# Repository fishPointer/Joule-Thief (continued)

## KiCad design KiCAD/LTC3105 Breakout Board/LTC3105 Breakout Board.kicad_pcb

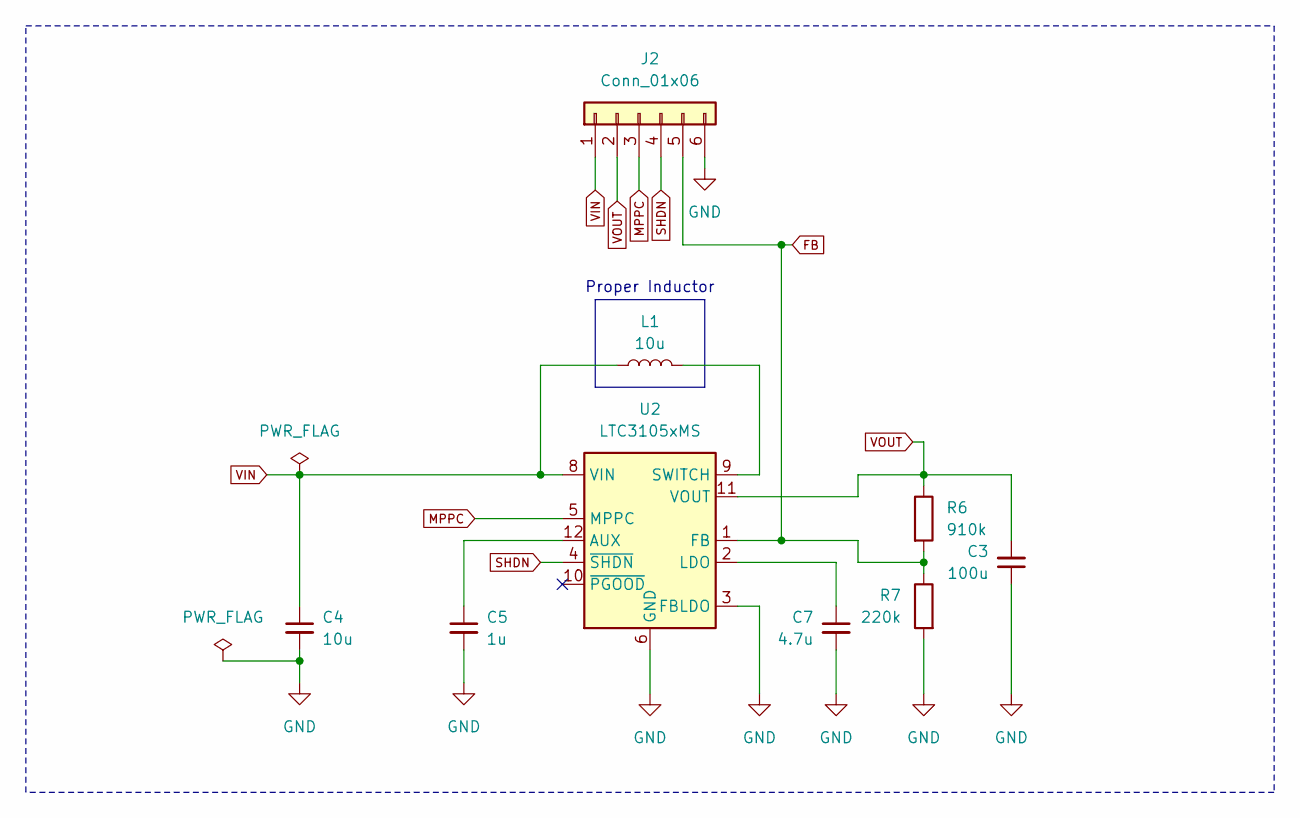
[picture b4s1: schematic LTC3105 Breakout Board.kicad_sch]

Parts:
C3: 100u; C_0805_2012Metric_Pad1.18x1.45mm_HandSolder
C4: 10u; C_0805_2012Metric_Pad1.18x1.45mm_HandSolder
C5: 1u; C_0805_2012Metric_Pad1.18x1.45mm_HandSolder
C7: 4.7u; C_0805_2012Metric_Pad1.18x1.45mm_HandSolder
J2: Conn_01x06; PinHeader_1x06_P1.27mm_Vertical
L1: 10u; Power_Inductor_101040
R6: 910k; PinHeader_1x02_P1.27mm_Vertical
R7: 220k; R_0805_2012Metric_Pad1.20x1.40mm_HandSolder
U2: LTC3105xMS; MSOP-12_3x4.039mm_P0.65mm

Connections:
FB: J2.5, R6.2, R7.1, U2.1 (FB)
GND: C3.1, C4.2, C5.2, C7.2, J2.6, R7.2, U2.3 (FBLDO), U2.6 (GND), U2.7 (GND)
MPPC: J2.3, U2.5 (MPPC)
unnamed: C5.1, U2.12 (AUX)
unnamed: C7.1, U2.2 (LDO)
unnamed: L1.2, U2.9 (SWITCH)
SHDN: J2.4, U2.4 (~SHDN)
VIN: C4.1, J2.1, L1.1, U2.8 (VIN)
VOUT: C3.2, J2.2, R6.1, U2.11 (VOUT)

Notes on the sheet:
Proper Inductor

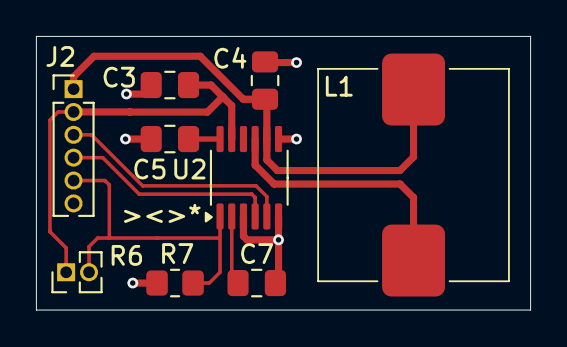
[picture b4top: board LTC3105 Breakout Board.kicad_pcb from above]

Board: 2 copper layers, 27.4 x 15.2 mm, 9 parts (0 on the bottom side), 9 nets.

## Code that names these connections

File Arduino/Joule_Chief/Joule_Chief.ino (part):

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bool schmittState = false;                  // Current state of Schmitt trigger output

// Charger Buffer Schmitt Trigger Parameters
const float SCHMITT_UPPER_THRESHOLD_2 = 5.25; // Upper threshold voltage for boost
const float SCHMITT_LOWER_THRESHOLD_2 = 4.25; // Lower threshold voltage for boost
bool schmittState2 = false;                    // Current state of second Schmitt trigger output

// ----------- DECLARATIONS -----------
// Analog and Digital I/O Pin Definitions
const int BOOST_PIN = 5;    // Chief Booster Enable HIGH
const int CHARGE_PIN = 6;   // Chief Charger Enable HIGH
const int SHDN_0_PIN = 13;  // Pull LOW to SHDN Module 0
const int SHDN_1_PIN = 12;  // Pull LOW to SHDN Module 1
const int SHDN_2_PIN = 11;  // Pull LOW to SHDN Module 2
const int SHDN_3_PIN = 10;  // Pull LOW to SHDN Module 3

// ----------- CHANNEL DATA STRUCTURE -----------
struct ChannelData {
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  Wire.setClock(400000);  // Set I2C clock to 400kHz for all devices

  // Initialize digital I/O pins
  pinMode(BOOST_PIN, OUTPUT);
  digitalWrite(BOOST_PIN, LOW);
  pinMode(CHARGE_PIN, OUTPUT);
  digitalWrite(CHARGE_PIN, LOW);
  pinMode(SHDN_0_PIN, OUTPUT);
  digitalWrite(SHDN_0_PIN, HIGH);
  pinMode(SHDN_1_PIN, OUTPUT);
  digitalWrite(SHDN_1_PIN, HIGH);
  pinMode(SHDN_2_PIN, OUTPUT);
  digitalWrite(SHDN_2_PIN, HIGH);
  pinMode(SHDN_3_PIN, OUTPUT);
  digitalWrite(SHDN_3_PIN, HIGH);

  // Initialize channels array
  initializeChannels();
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    if (schmittState == false) {
      if (sourceVoltageA >= SCHMITT_UPPER_THRESHOLD) {
        schmittState = true;
        digitalWrite(BOOST_PIN, HIGH);
      }
    } else {
      if (sourceVoltageA <= SCHMITT_LOWER_THRESHOLD) {
        schmittState = false;
        digitalWrite(BOOST_PIN, LOW);
      }
    }
  }
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
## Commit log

2025-03-05 init
2025-03-05 prune junk
2025-03-05 wire up batteries
2025-03-14 new pcb revision
2025-03-15 made pcb r3, start r4
2025-03-15 r5 is the one bro i swear
2025-03-19 board ordered
2025-06-23 INA219 firmware+LTC3105 breakout
2025-06-30 fw dev + r1 schematic
2025-07-01 joule chief shield schematic
2025-07-01 both schematics finished
2025-07-01 ERC+prep for board layout
2025-07-03 layout extraction module
2025-08-05 repo cleanup for final writeup
